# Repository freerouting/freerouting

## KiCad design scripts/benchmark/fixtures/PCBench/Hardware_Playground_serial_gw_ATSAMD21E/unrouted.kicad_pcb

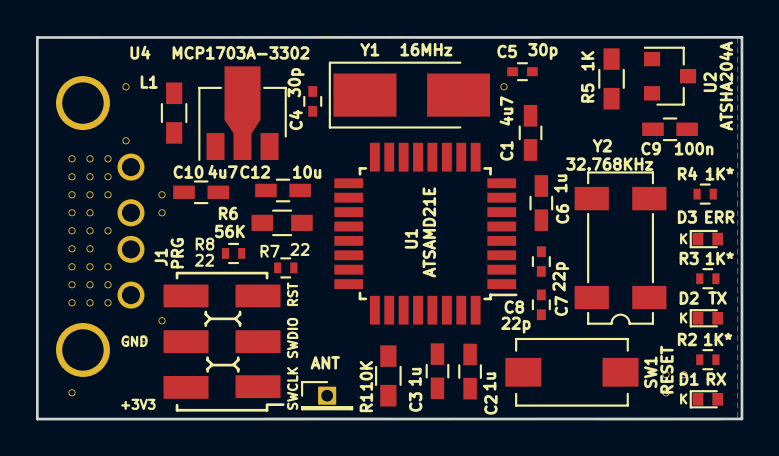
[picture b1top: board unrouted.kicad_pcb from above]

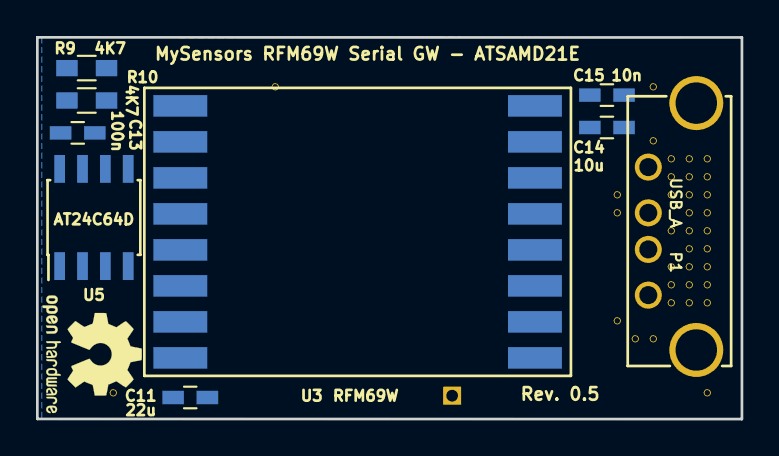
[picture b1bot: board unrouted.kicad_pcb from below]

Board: 2 copper layers, 39.1 x 21.2 mm, 77 parts (8 on the bottom side), 32 nets, no tracks yet.

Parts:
C1, C10: 4u7; C_0603_HandSoldering
C2, C3, C6: 1u; C_0603_HandSoldering
C4, C5: 30p; C_0402
C7, C8: 22p; C_0402
C9, C13: 100n; C_0603_HandSoldering
C11: 22u; C_0603_HandSoldering
C12, C14: 10u; C_0603_HandSoldering
C15: 10n; C_0603_HandSoldering
D1: RX; LED_0402
D2: TX; LED_0402
D3: ERR; LED_0402
J1: PRG; AVR_ISP_SMT_Small_02x03
L1: BLM18HE152SN1D; R_0603_HandSoldering
P1: USB_A; USB_A_bottom
P2: ANT; Pin_Header_Straight_1x01_Pitch1.27mm
R1: 10K; R_0603_HandSoldering
R2, R3, R4: 1K*; R_0402
R5: 1K; R_0603_HandSoldering
R6: 56K; R_0603_HandSoldering
R7, R8: 22; R_0402
R9, R10: 4K7; R_0603_HandSoldering
SW1: RESET; SW_SPST_EVQPE1
U1: ATSAMD21E; TQFP-32_7x7mm_Pitch0.8mm
U2: ATSHA204A; SOT-23
U3: RFM69W; RFM69HW_SMD_Handsoldering
U4: MCP1703A-3302; SOT89-3_Housing
U5: AT24C64D; SOIC-8_3.9x4.9mm_Pitch1.27mm
V2_7, V2_8, V2_9, V2_10, V2_11, V2_12, V2_13, V2_14, V2_15, V2_20, V3_7, V3_8, V3_9, V3_10, V3_11, V3_12, V3_13, V3_14, V3_15, V4_7, V4_8, V4_9, V4_11, V4_13, V4_14, V4_15, V5_3, V5_6, V5_17, V6_17, V7_9, V7_10, V7_16, V26_3, V35_19, V35_20, V36_19: AUTO_VIA; VIA_MATRIX
Y1: 16MHz; Crystal_SMD_5032-2pin_5.0x3.2mm_HandSoldering
Y2: 32.768KHz; Crystal_SMD_SeikoEpson_MC306-4pin_8.0x3.2mm

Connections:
+3V3: C1.1, C2.2, C9.1, C11.1, C12.1, C13.1, J1.2, R1.2, R5.2, R6.2, R9.2, R10.2, U1.9, U1.30, U2.2, U3.8, U4.3, U5.1, U5.3, U5.8
/ATSHA204A: R5.1, U1.8, U2.1
/GW_ERR_LED: R4.2, U1.7
/GW_RX_LED: R2.2, U1.3
/GW_TX_LED: R3.2, U1.5
/MISO: U1.21, U3.13
/MOSI: U1.19, U3.14
/RFM69W_INT: U1.6, U3.2
/RFM69W_SS: R6.1, U1.22, U3.15
/RST: J1.5, R1.1, SW1.1, U1.26
/SCK: U1.20, U3.12
/SCL: R10.1, U1.18, U5.6
/SDA: R9.1, U1.17, U5.5
/SWCLK: J1.1, U1.31
/SWDIO: J1.3, U1.32
/USBDM: R8.1, U1.23
/USBDP: R7.1, U1.24
/VBUS: C10.1, C15.2, L1.2, U4.2
GND: C1.2, C2.1, C3.2, C4.2, C5.2, C6.2, C7.2, C8.2, C9.2, C10.2, C11.2, C12.2, C13.2, C14.1, C15.1, D1.1, D2.1, D3.1, J1.4, J1.6, P1.4, P1.5, SW1.2, U1.10, U1.28, U2.3, U3.9, U3.11, U4.1, U5.2, U5.4, U5.7, V2_7.1, V2_8.1, V2_9.1, V2_10.1, V2_11.1, V2_12.1, V2_13.1, V2_14.1, V2_15.1, V2_20.1, V3_7.1, V3_8.1, V3_9.1, V3_10.1, V3_11.1, V3_12.1, V3_13.1, V3_14.1, V3_15.1, V4_7.1, V4_8.1, V4_9.1, V4_11.1, V4_13.1, V4_14.1, V4_15.1, V5_3.1, V5_6.1, V5_17.1, V6_17.1, V7_9.1, V7_10.1, V7_16.1, V26_3.1, V35_19.1, V35_20.1, V36_19.1
unnamed: C3.1, U1.29
unnamed: C4.1, U1.16, Y1.1
unnamed: C5.1, U1.15, Y1.2
unnamed: C6.1, U1.4
unnamed: C7.1, U1.2, Y2.1
unnamed: C8.1, U1.1, Y2.4
unnamed: C14.2, L1.1, P1.1
unnamed: D1.2, R2.1
unnamed: D2.2, R3.1
unnamed: D3.2, R4.1
unnamed: P1.2, R8.2
unnamed: P1.3, R7.2
unnamed: P2.1, U3.10

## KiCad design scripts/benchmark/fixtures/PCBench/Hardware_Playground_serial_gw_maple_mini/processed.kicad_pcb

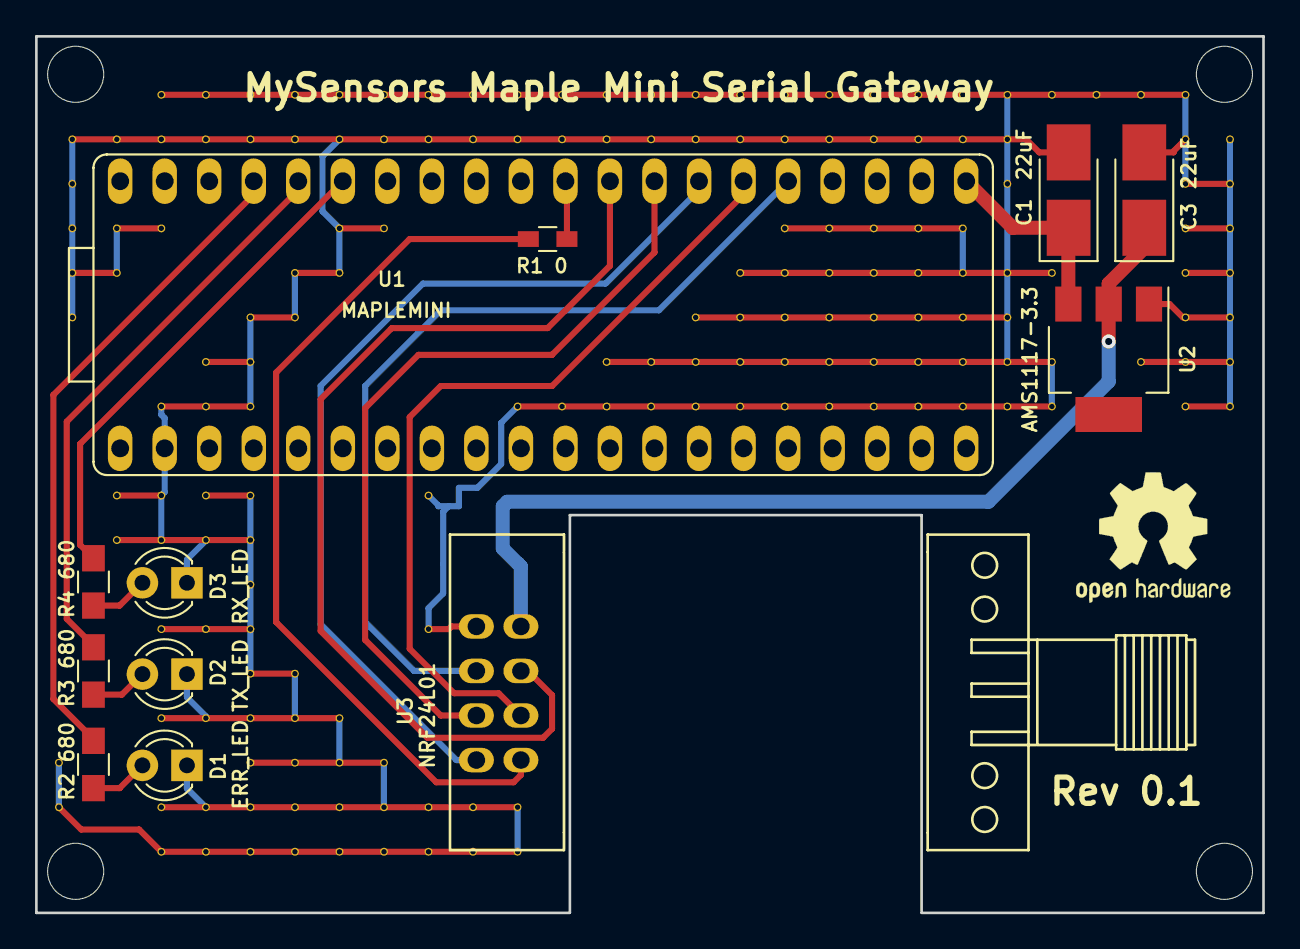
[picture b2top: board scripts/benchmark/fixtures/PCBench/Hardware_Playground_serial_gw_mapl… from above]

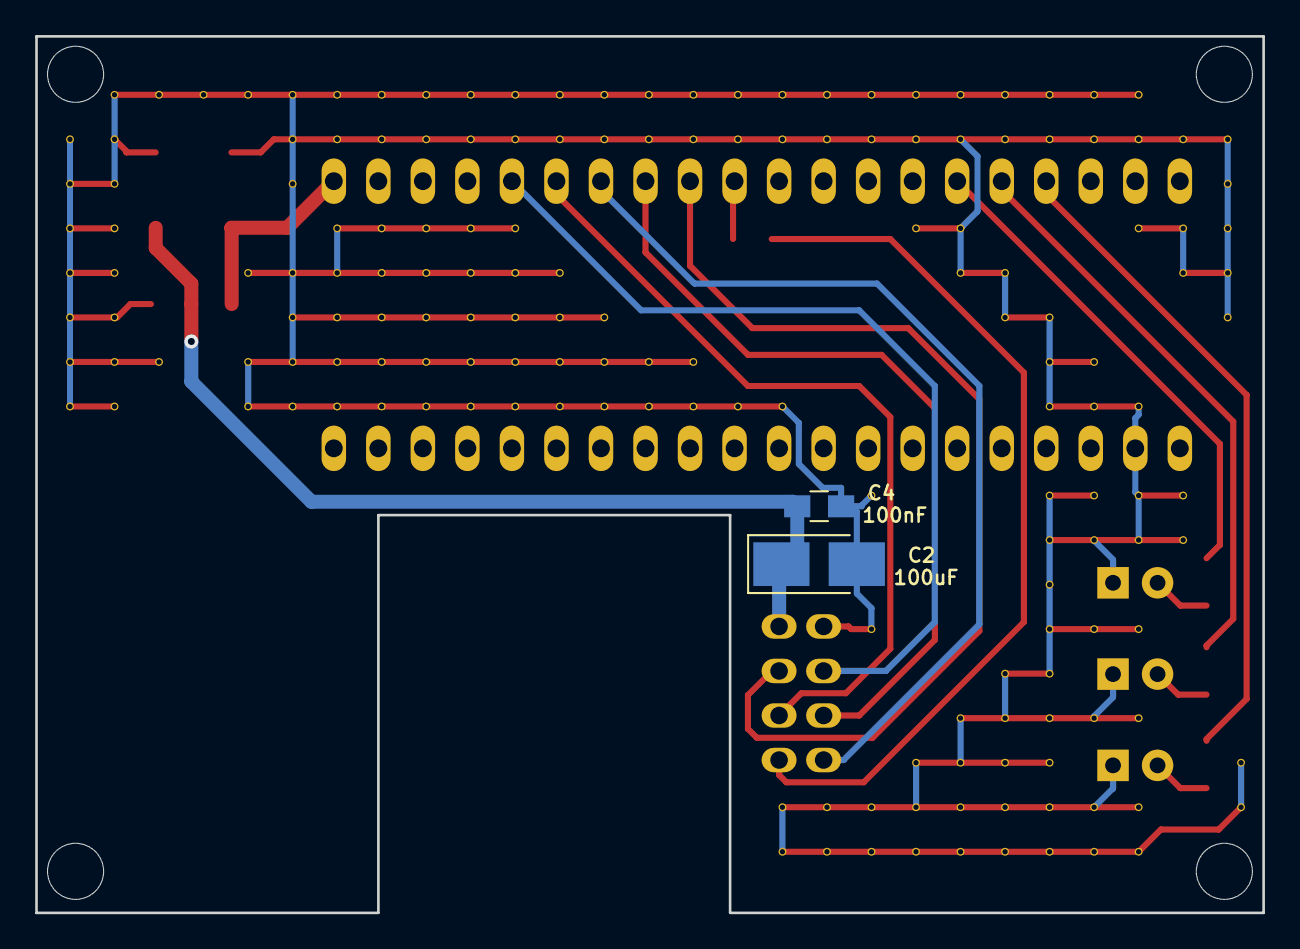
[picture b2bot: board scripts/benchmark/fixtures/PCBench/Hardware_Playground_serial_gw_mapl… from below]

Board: 2 copper layers, 70.0 x 50.0 mm, 184 parts (2 on the bottom side), 16 nets.

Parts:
C1, C3: 22uF; CP_Tantalum_Case-B_EIA-3528-21_Hand
C2: 100uF; CP_Tantalum_Case-B_EIA-3528-21_Hand
C4: 100nF; C_0805_HandSoldering
D1: ERR_LED; LED_D3.0mm
D2: TX_LED; LED_D3.0mm
D3: RX_LED; LED_D3.0mm
R1: 0; R_0603_HandSoldering
R2, R3, R4: 680; R_0805_HandSoldering
U1: MAPLEMINI; MAPLE_MINI
U2: AMS1117-3.3; SOT-223
U3: NRF24L01; E01-ML01DP5
V3_4, V3_5, V3_6, V3_7, V3_8, V3_18, V3_19, V4_4, V4_6, V4_7, V4_12, V4_13, V5_3, V5_4, V5_6, V5_10, V5_12, V5_13, V5_15, V5_17, V5_19, V5_20, V6_3, V6_4, V6_9, V6_10, V6_12, V6_13, V6_15, V6_17, V6_19, V6_20, V7_3, V7_4, V7_8, V7_9, V7_10, V7_12, V7_13, V7_14, V7_15, V7_16, V7_17, V7_18, V7_19, V7_20, V8_3, V8_4, V8_7, V8_8, V8_16, V8_17, V8_18, V8_19, V8_20, V9_3, V9_4, V9_6, V9_7, V9_17, V9_18, V9_19, V9_20, V10_3, V10_4, V10_6, V10_18, V10_19, V10_20, V11_3, V11_4, V11_12, V11_15, V11_19, V11_20, V12_3, V12_4, V12_19, V12_20, V13_3, V13_4, V13_10, V13_19, V13_20, V14_3, V14_4, V14_10, V15_3, V15_4, V15_9, V15_10, V16_3, V16_4, V16_9, V16_10, V17_3, V17_4, V17_8, V17_9, V17_10, V18_3, V18_4, V18_7, V18_8, V18_9, V18_10, V19_3, V19_4, V19_6, V19_7, V19_8, V19_9, V19_10, V20_3, V20_4, V20_6, V20_7, V20_8, V20_9, V20_10, V21_3, V21_4, V21_6, V21_7, V21_8, V21_9, V21_10, V22_3, V22_4, V22_6, V22_7, V22_8, V22_9, V22_10, V23_3, V23_4, V23_6, V23_7, V23_8, V23_9, V23_10, V24_3, V24_4, V24_5, V24_7, V24_8, V24_9, V24_10, V25_3, V25_7, V25_9, V25_10, V26_3, V27_3, V27_9, V28_3, V28_4, V28_5, V28_6, V28_7, V28_8, V28_9, V28_10, V29_4, V29_5, V29_6, V29_7, V29_8, V29_9, V29_10: AUTO_VIA; VIA_MATRIX

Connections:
+3V3: C2.1, C3.1, C4.1, U2.2, U3.2
/ERR_LED: R2.2, U1.37
/MAPLE_VIN: C1.1, U1.21, U2.3
/NRF24_IRQ: R1.1, U3.8
/RX_LED: R4.2, U1.35
/SPI_CE: U1.25, U3.3
/SPI_CSN: U1.29, U3.4
/SPI_MISO: U1.27, U3.7
/SPI_MOSI: U1.26, U3.6
/SPI_SCK: U1.28, U3.5
/TX_LED: R3.2, U1.36
GND: C1.2, C2.2, C3.2, C4.2, D1.1, D2.1, D3.1, U1.2, U2.1, U3.1, V3_4.1, V3_5.1, V3_6.1, V3_7.1, V3_8.1, V3_18.1, V3_19.1, V4_4.1, V4_6.1, V4_7.1, V4_12.1, V4_13.1, V5_3.1, V5_4.1, V5_6.1, V5_10.1, V5_12.1, V5_13.1, V5_15.1, V5_17.1, V5_19.1, V5_20.1, V6_3.1, V6_4.1, V6_9.1, V6_10.1, V6_12.1, V6_13.1, V6_15.1, V6_17.1, V6_19.1, V6_20.1, V7_3.1, V7_4.1, V7_8.1, V7_9.1, V7_10.1, V7_12.1, V7_13.1, V7_14.1, V7_15.1, V7_16.1, V7_17.1, V7_18.1, V7_19.1, V7_20.1, V8_3.1, V8_4.1, V8_7.1, V8_8.1, V8_16.1, V8_17.1, V8_18.1, V8_19.1, V8_20.1, V9_3.1, V9_4.1, V9_6.1, V9_7.1, V9_17.1, V9_18.1, V9_19.1, V9_20.1, V10_3.1, V10_4.1, V10_6.1, V10_18.1, V10_19.1, V10_20.1, V11_3.1, V11_4.1, V11_12.1, V11_15.1, V11_19.1, V11_20.1, V12_3.1, V12_4.1, V12_19.1, V12_20.1, V13_3.1, V13_4.1, V13_10.1, V13_19.1, V13_20.1, V14_3.1, V14_4.1, V14_10.1, V15_3.1, V15_4.1, V15_9.1, V15_10.1, V16_3.1, V16_4.1, V16_9.1, V16_10.1, V17_3.1, V17_4.1, V17_8.1, V17_9.1, V17_10.1, V18_3.1, V18_4.1, V18_7.1, V18_8.1, V18_9.1, V18_10.1, V19_3.1, V19_4.1, V19_6.1, V19_7.1, V19_8.1, V19_9.1, V19_10.1, V20_3.1, V20_4.1, V20_6.1, V20_7.1, V20_8.1, V20_9.1, V20_10.1, V21_3.1, V21_4.1, V21_6.1, V21_7.1, V21_8.1, V21_9.1, V21_10.1, V22_3.1, V22_4.1, V22_6.1, V22_7.1, V22_8.1, V22_9.1, V22_10.1, V23_3.1, V23_4.1, V23_6.1, V23_7.1, V23_8.1, V23_9.1, V23_10.1, V24_3.1, V24_4.1, V24_5.1, V24_7.1, V24_8.1, V24_9.1, V24_10.1, V25_3.1, V25_7.1, V25_9.1, V25_10.1, V26_3.1, V27_3.1, V27_9.1, V28_3.1, V28_4.1, V28_5.1, V28_6.1, V28_7.1, V28_8.1, V28_9.1, V28_10.1, V29_4.1, V29_5.1, V29_6.1, V29_7.1, V29_8.1, V29_9.1, V29_10.1
unnamed: D1.2, R2.1
unnamed: D2.2, R3.1
unnamed: D3.2, R4.1
unnamed: R1.2, U1.30

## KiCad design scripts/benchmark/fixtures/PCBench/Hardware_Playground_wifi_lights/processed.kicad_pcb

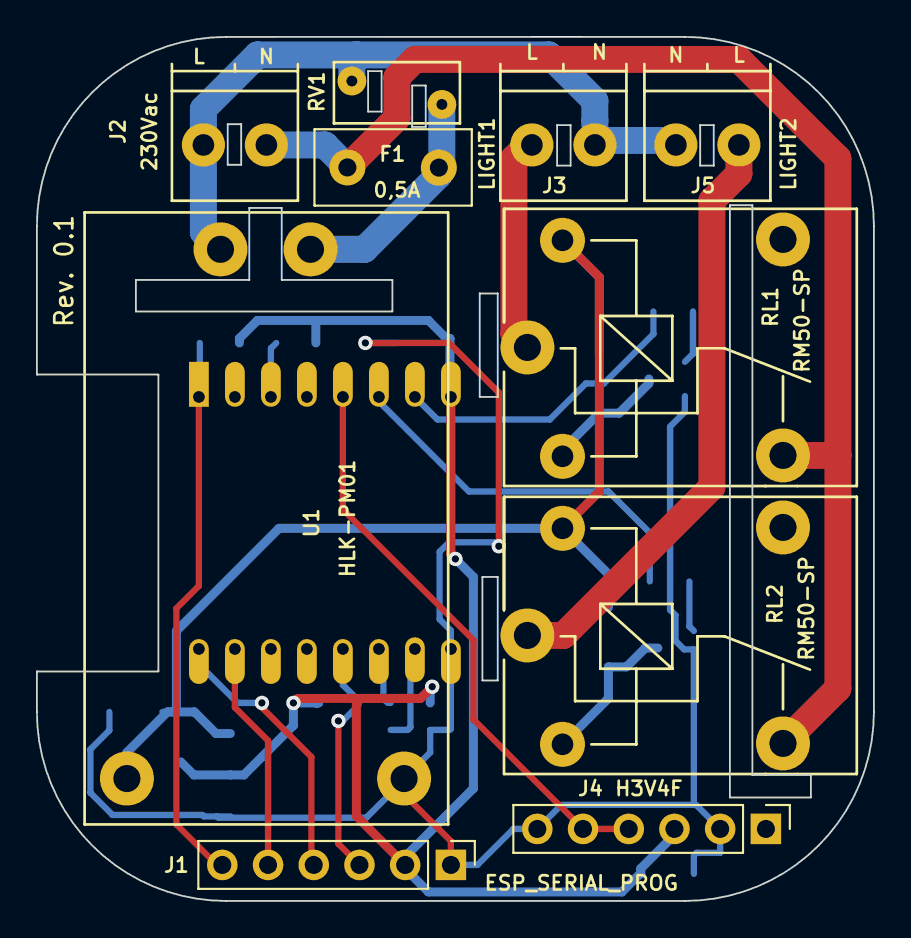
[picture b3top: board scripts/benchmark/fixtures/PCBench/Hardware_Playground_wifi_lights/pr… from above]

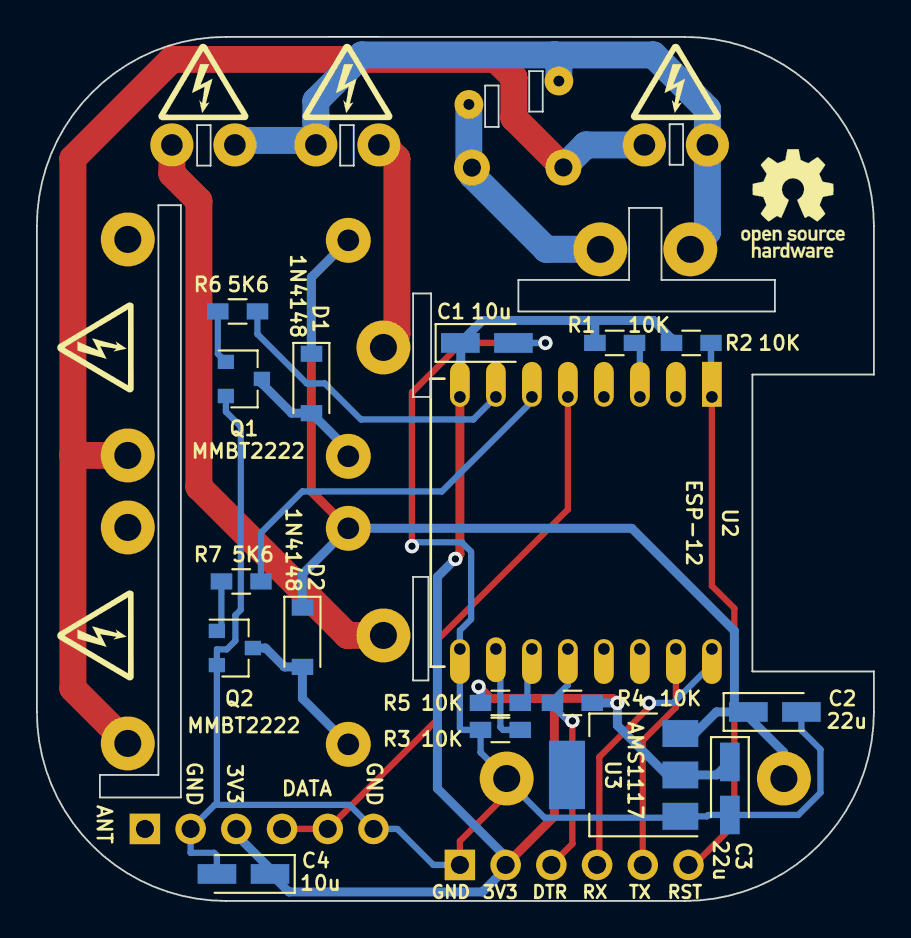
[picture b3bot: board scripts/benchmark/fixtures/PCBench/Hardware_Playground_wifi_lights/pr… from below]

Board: 2 copper layers, 46.5 x 48.0 mm, 27 parts (17 on the bottom side), 22 nets.

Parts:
C1, C4: 10u; CP_Tantalum_Case-A_EIA-3216-18_Wave
C2, C3: 22u; CP_Tantalum_Case-A_EIA-3216-18_Wave
D1, D2: 1N4148; D_SOD-123
F1: 0,5A; Fuse_TE5_Littlefuse-395Series
J1: ESP_SERIAL_PROG; Pin_Header_Straight_1x06_Pitch2.54mm
J2: 230Vac; TerminalBlock_Pheonix_PT-3.5mm_2pol
J3: LIGHT1; TerminalBlock_Pheonix_PT-3.5mm_2pol
J4: H3V4F; Pin_Header_Straight_1x06_Pitch2.54mm
J5: LIGHT2; TerminalBlock_Pheonix_PT-3.5mm_2pol
Q1, Q2: MMBT2222; SOT-23
R1, R2, R3, R4, R5: 10K; R_0603_HandSoldering
R6, R7: 5K6; R_0603_HandSoldering
RL1, RL2: RM50-SP; RM50_P
RV1: Varistor; RV_Disc_D7_W3.4_P5
U1: ESP-12
U2: HLK-PM01
U3: AMS1117; SOT-223

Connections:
+3V3: C1.1, C3.1, C4.1, J1.2, J4.3, R1.2, R2.2, R4.2, R5.2, U1.8, U3.2
+5V: C2.1, D1.1, D2.1, RL1.A1, RL2.A1, U2.3, U3.3
/433_RX_DATA: J4.4, J4.5, U1.5
/DTR: J1.3, R4.1, U1.12
/L: F1.1, J2.1, RL1.14, RL2.14
/N: J2.2, J3.1, J5.2, RV1.2, U2.2
/RELAY_CH1: R6.2, U1.7
/RELAY_CH2: R7.2, U1.6
/REL_SW1: J3.2, RL1.11
/REL_SW2: J5.1, RL2.11
/RESET: J1.6, R2.1, U1.1
/RX: J1.4, U1.16
/TX: J1.5, U1.15
GND: C1.2, C2.2, C3.2, C4.2, J1.1, J4.2, J4.6, Q1.2, Q2.2, R3.1, U1.9, U2.4, U3.1
unnamed: D1.2, Q1.3, RL1.A2
unnamed: D2.2, Q2.3, RL2.A2
unnamed: F1.2, RV1.1, U2.1
unnamed: Q1.1, R6.1
unnamed: Q2.1, R7.1
unnamed: R1.1, U1.3
unnamed: R3.2, U1.10
unnamed: R5.1, U1.11
